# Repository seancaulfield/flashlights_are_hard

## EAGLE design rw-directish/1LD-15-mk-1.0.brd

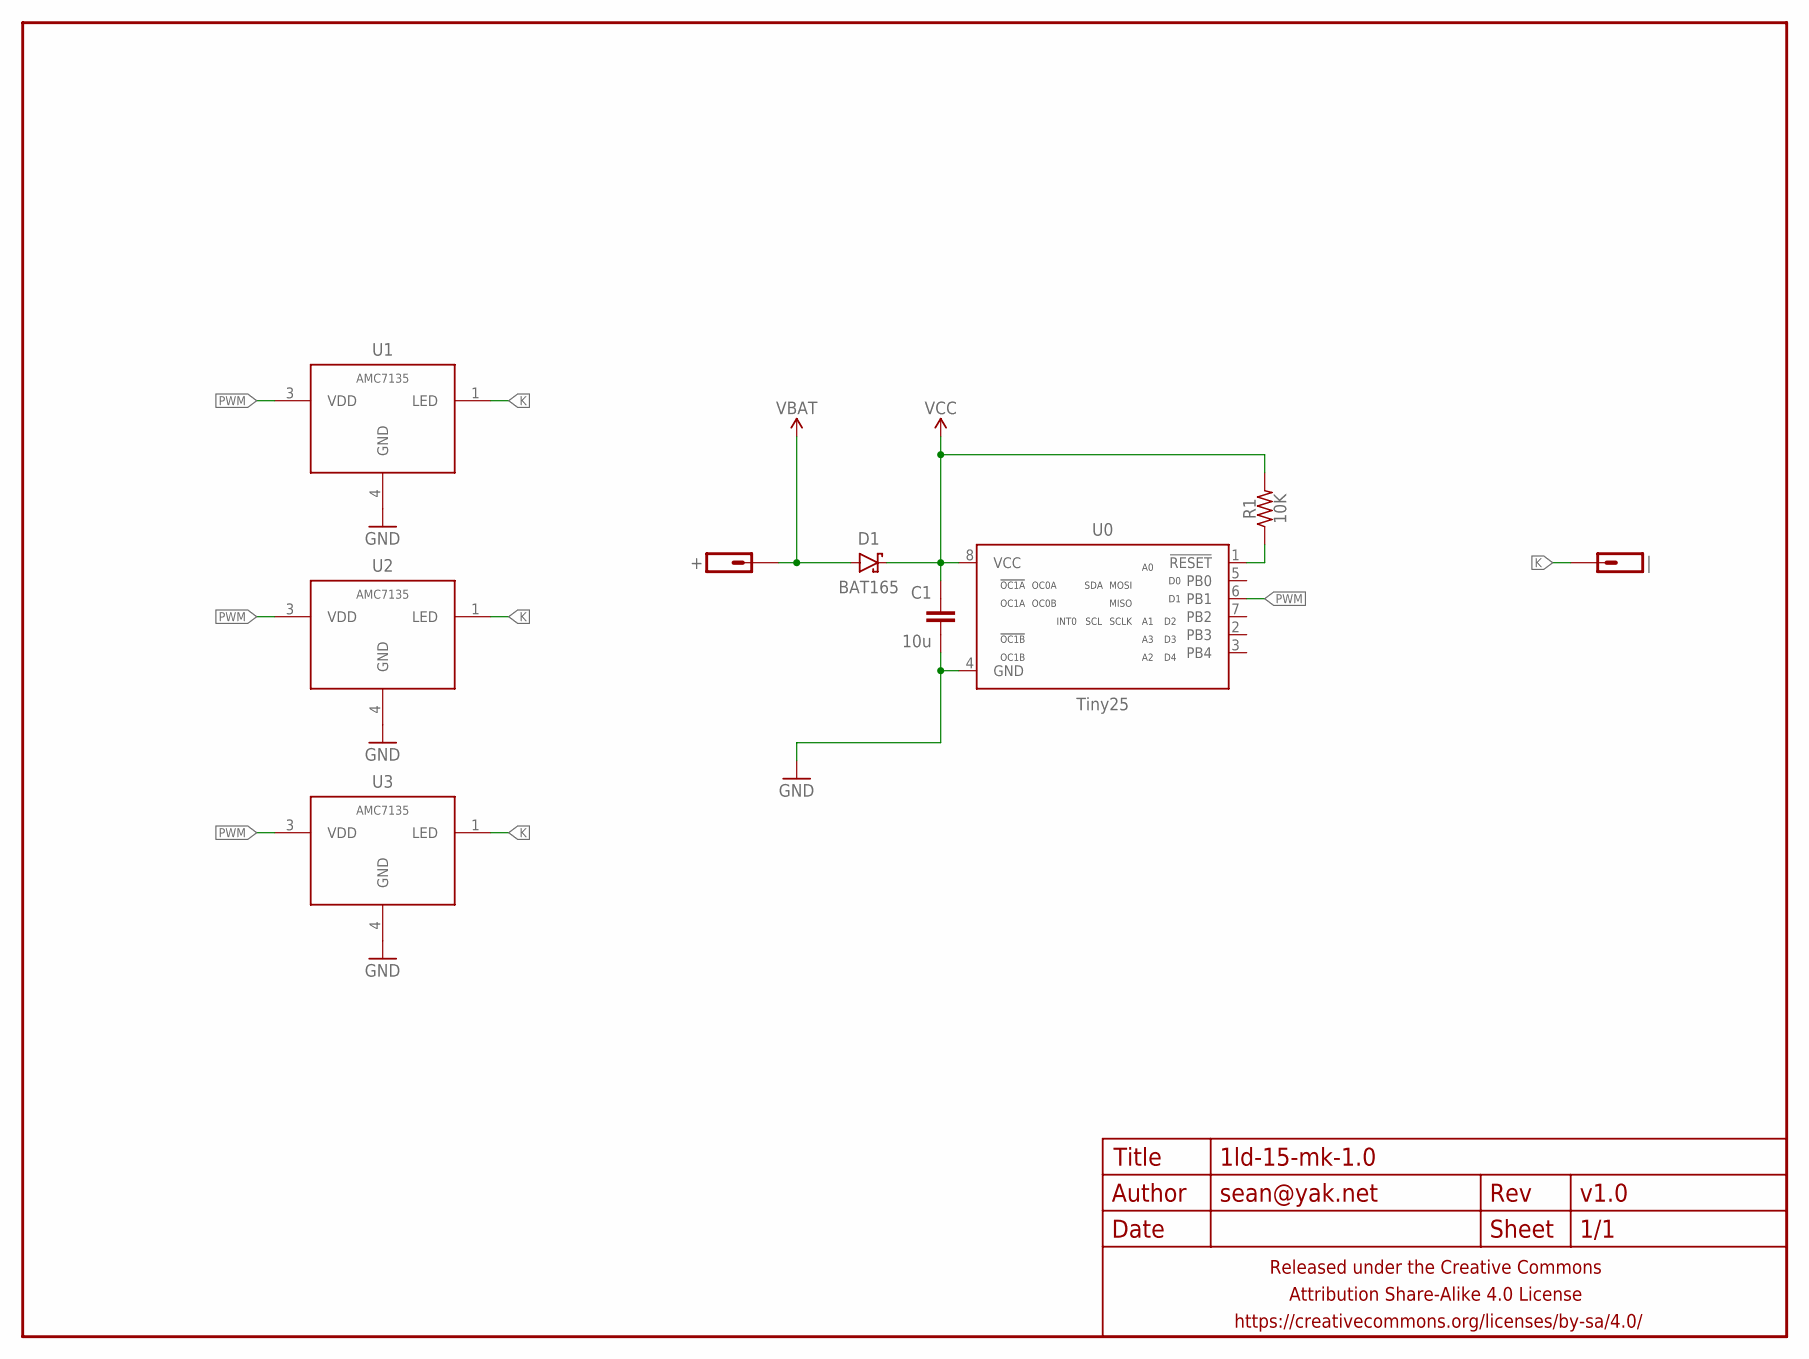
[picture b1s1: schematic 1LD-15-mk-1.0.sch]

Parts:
+: M01PTH-0.8MM-CIR; 1X01-0.8MM-CIR
C1: 10u; C0603-TIGHTER
D1: BAT165; SOD-123-SCHOTTYK-ROUND
FRAME1: FRAME-LETTERNO_PACKAGE; DUMMY
R1: 10K; R0603-TIGHTER
U0: Tiny25; SO08-NARROWER
U1, U2, U3: AMC7135; SOT89-NOTHERM-ROUNDED-LESS
|: M01PTH-0.8MM-CIR; 1X01-0.8MM-CIR

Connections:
GND: C1.2, U0.4 (GND), U1.4 (GND), U2.4 (GND), U3.4 (GND)
K: U1.1 (LED), U2.1 (LED), U3.1 (LED), |.1
unnamed: R1.1, U0.1 (!RESET)
PWM: U0.6 (PB1), U1.3 (VDD), U2.3 (VDD), U3.3 (VDD)
VBAT: +.1, D1.A
VCC: C1.1, D1.C, R1.2, U0.8 (VCC)

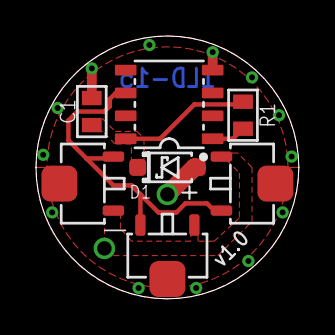
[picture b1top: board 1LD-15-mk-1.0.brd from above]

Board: 2 copper layers, 14.6 x 14.6 mm, 10 parts (0 on the bottom side), 6 nets.

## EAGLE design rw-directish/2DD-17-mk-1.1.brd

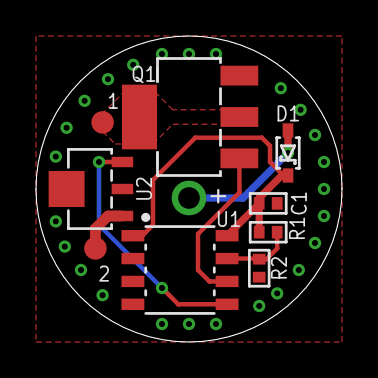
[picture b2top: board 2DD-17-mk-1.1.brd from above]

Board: 2 copper layers, 17.0 x 17.0 mm, 12 parts (1 on the bottom side), 8 nets.

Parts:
1, 2: M01SMD-1.25MM-DIA; 1X01-SMD-1.25MM-DIA-NS
+: M01PTH-1.2MM-NS; 1X01-1.2MM-NS
-: M01NOT-A-VIA-NOPE; 1X01_NOSILK_NOSTOP
C1: 1u; C0402
D1: BAT165; SOD323-SCHOTTKY
FRAME1: FRAME-LETTERNO_PACKAGE; DUMMY
Q1: MOSFET-NCHANNELSOT-223-CLOSER; SOT223-CLOSER
R1: 19K; R0402
R2: 4K7; R0402
U1: ATTiny13; SO08-NARROWER
U2: AMC7135SOT-89-NOTHERM; SOT89-NOTHERM

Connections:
GND: -.P$1, C1.2, Q1.3, R2.1, U1.4, U2.4@1, U2.4@2
unnamed: R1.1, R2.2, U1.7
PWM_R: U1.5, U2.3
PWM_W: Q1.1, U1.6
R: 2.P$1, U2.1
VBAT: +.P$1, D1.A
VCC: C1.1, D1.C, R1.2, U1.1, U1.8
W: 1.P$1, Q1.2, Q1.4

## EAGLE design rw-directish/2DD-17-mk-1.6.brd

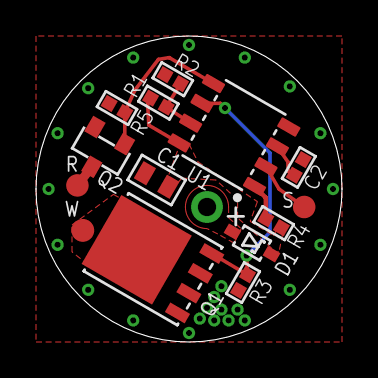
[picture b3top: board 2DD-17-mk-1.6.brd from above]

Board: 2 copper layers, 17.0 x 17.0 mm, 17 parts (1 on the bottom side), 11 nets.

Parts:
+: M01PTH-1MM-CIR-NS; 1X01-1MM-CIR-NS
-: M01NOT-A-VIA-NOPE; 1X01_NOSILK_NOSTOP
C1: 10u; C0603-TIGHTER
C2: 1u; C0402
D1: BAT165; SOD323-SCHOTTKY
FRAME1: FRAME-LETTERNO_PACKAGE; DUMMY
Q1: SIR800DP; POWERPACK-SO-8
Q2: IRLML2502; SOT23-CLOSER
R: M01SMD-1.25MM-DIA; 1X01-SMD-1.25MM-DIA-NS
R1: 19K; R0402
R2: 4K7; R0402
R3, R5: 47K; R0402
R4: 10K; R0402
S: M01SMD-1.25MM-DIA; 1X01-SMD-1.25MM-DIA-NS
U1: Tiny13; SO08-NARROWER
W: M01NOSTOP-CANTSTOP-DONTKNOWHOWTOSTOP; 1X01_SMD_NOSTOP_NOSILK

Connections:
GND: -.P$1, C1.2, C2.2, Q1.1, Q1.2, Q1.3, Q2.2, R2.1, R3.2, R5.2, U1.4
OTC: C2.1, U1.3
PWM_R: Q2.1, R5.1, U1.5
PWM_W: Q1.4, R3.1, U1.6
R: Q2.3, R.P$1
RESET: R4.1, U1.1
SWITCH: S.P$1, U1.2
VBAT: +.1, D1.A
VCC: C1.1, D1.C, R1.2, R4.2, U1.8
VDIV: R1.1, R2.2, U1.7
W: Q1.5678, W.1

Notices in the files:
parts and their libraries:
a_parts: Released under the Creative Commons Attribution Share-Alike 4.0 License
a_parts: https://creativecommons.org/licenses/by-sa/4.0
a_parts: Released under the Creative Commons
